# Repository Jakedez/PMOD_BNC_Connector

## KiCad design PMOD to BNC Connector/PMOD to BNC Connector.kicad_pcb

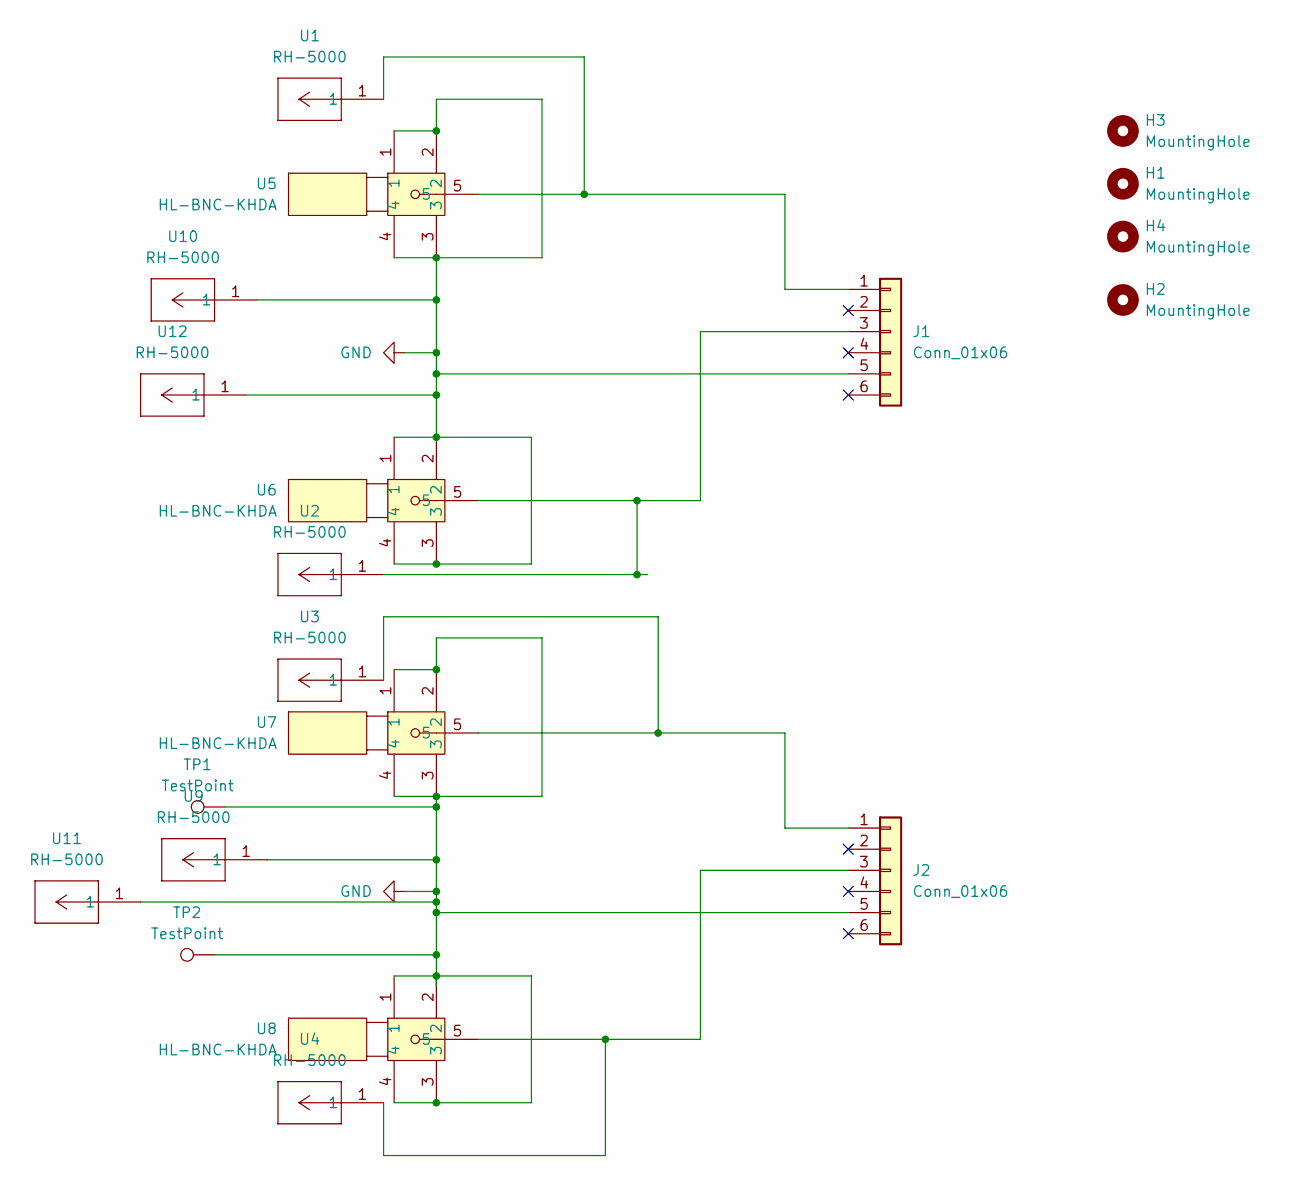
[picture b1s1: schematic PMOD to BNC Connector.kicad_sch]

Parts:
H1, H2, H3, H4: MountingHole; MountingHole_3.5mm
J1, J2: Conn_01x06; PinHeader_1x06_P2.54mm_Vertical
TP1, TP2: TestPoint; TestPoint_Pad_4.0x4.0mm
U1, U2, U3, U4, U9, U10, U11, U12: RH-5000; CONN1_1514-2_KEY; Mouser Part Number 534-1514-2; LCSC Part C5277086
U5, U6, U7, U8: HL-BNC-KHDA; BNC-TH_L12.0-W12.0; LCSC Part C19712152

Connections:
GND: J1.5, J2.5, TP1.1, TP2.1, U5.1, U5.2, U5.3, U5.4, U6.1, U6.2, U6.3, U6.4, U7.1, U7.2, U7.3, U7.4, U8.1, U8.2, U8.3, U8.4, U9.1, U10.1, U11.1, U12.1
unnamed: J1.1, U1.1, U5.5
unnamed: J1.3, U2.1, U6.5
unnamed: J2.1, U3.1, U7.5
unnamed: J2.3, U4.1, U8.5

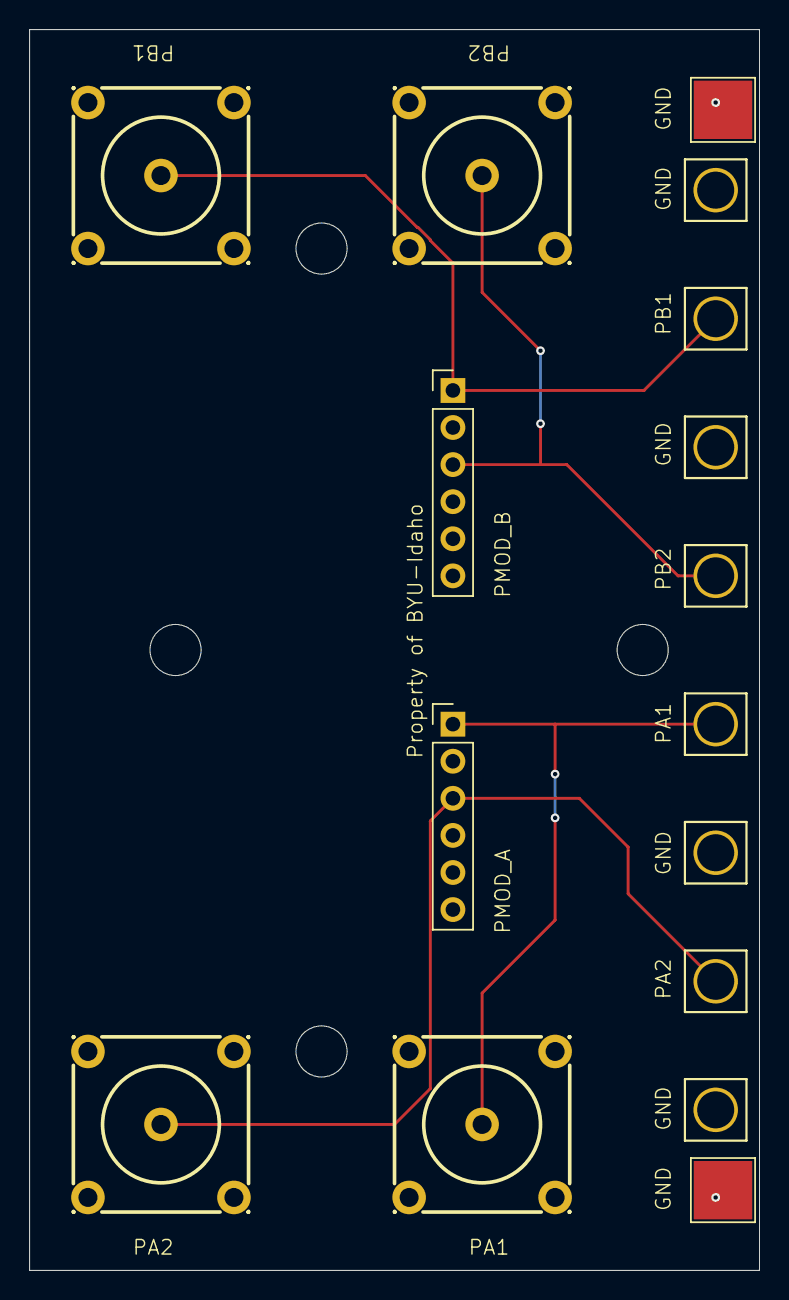
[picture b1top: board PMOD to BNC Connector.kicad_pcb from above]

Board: 2 copper layers, 50.0 x 85.0 mm, 20 parts (0 on the bottom side), 5 nets.

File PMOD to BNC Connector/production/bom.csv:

Designator,Footprint,Quantity,Value,LCSC Part #
"J1, J2",PinHeader_1x06_P2.54mm_Vertical,2,Conn_01x06,
"TP1, TP2",TestPoint_Pad_4.0x4.0mm,2,TestPoint,
"U1, U10, U11, U12, U2, U3, U4, U9",CONN1_1514-2_KEY,8,RH-5000,C5277086
"U5, U6, U7, U8",BNC-TH_L12.0-W12.0,4,HL-BNC-KHDA,C19712152

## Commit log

2026-02-14 EVERYTHING
2026-02-14 "Sorry"
2026-02-14 Added Ground Test Points
2026-02-17 Fixed 3D models to local project paths
2026-02-17 More paths adjusted to local project
2026-02-17 Updated production generated components
2026-03-17 V2 Complete
2026-03-17 Version 2 Changes complete:
    Thermal Relief for Ground-plane connected devices
    Additional Mounting Holes Added
    Additional Test Points to Ground Added
    Cutout segment removed.
2026-03-17 Small tweaks
